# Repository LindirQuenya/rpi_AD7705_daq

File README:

Test / demo program for the AD7705 connected to the raspberry PI!
=================================================================

The AD7705 is a two channel sigma delta converter which has
differential inputs, a PGA and programmable data rates. It's
perfect for slowly changing inputs such as pressure, temperature,
heart rate etc.

The program is interrupt driven and can thus run in a thread
which is woken up by the interrupt. The clock for the ADC is
generated by directly manipulating the registers of the BCM
chip.

This program switches on the clock from the RPI, 
triggers a calibration of the AD, 
reads data from channel 1 and 
prints it on the screen.

This program uses DRDY connected to Port 22 and
waits for a falling edge on this port to read
the data. This is done via interrupts / poll
so that this process sleeps until new data becomes
available.

The design files are in the subdirectory "pcb".

To build:

    make

Run it with the command:

    sudo ./ad7705_test

Associated website:
http://web.eng.gla.ac.uk/rpi/

Bernd Porr
mail@berndporr.me.uk
www.berndporr.me.uk

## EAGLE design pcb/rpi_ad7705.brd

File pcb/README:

This work is licensed under a Creative Commons Attribution-NonCommercial 3.0 Unported License.
(C) 2013-2020 BERND PORR, www.berndporr.me.uk

This is an extension board which adds two analogue inputs to the Raspberry PI.
Three GPIO pins are also forwarded to another pin header with additional
input protection.

The AD7705 is a high preceision sigma delta converter with differential
inputs, buffers and a PGA. It's especially designed to measure small voltages,
for example from a pressure gauge or a thermocpuple.

The maximum sampling rate is 500Hz.

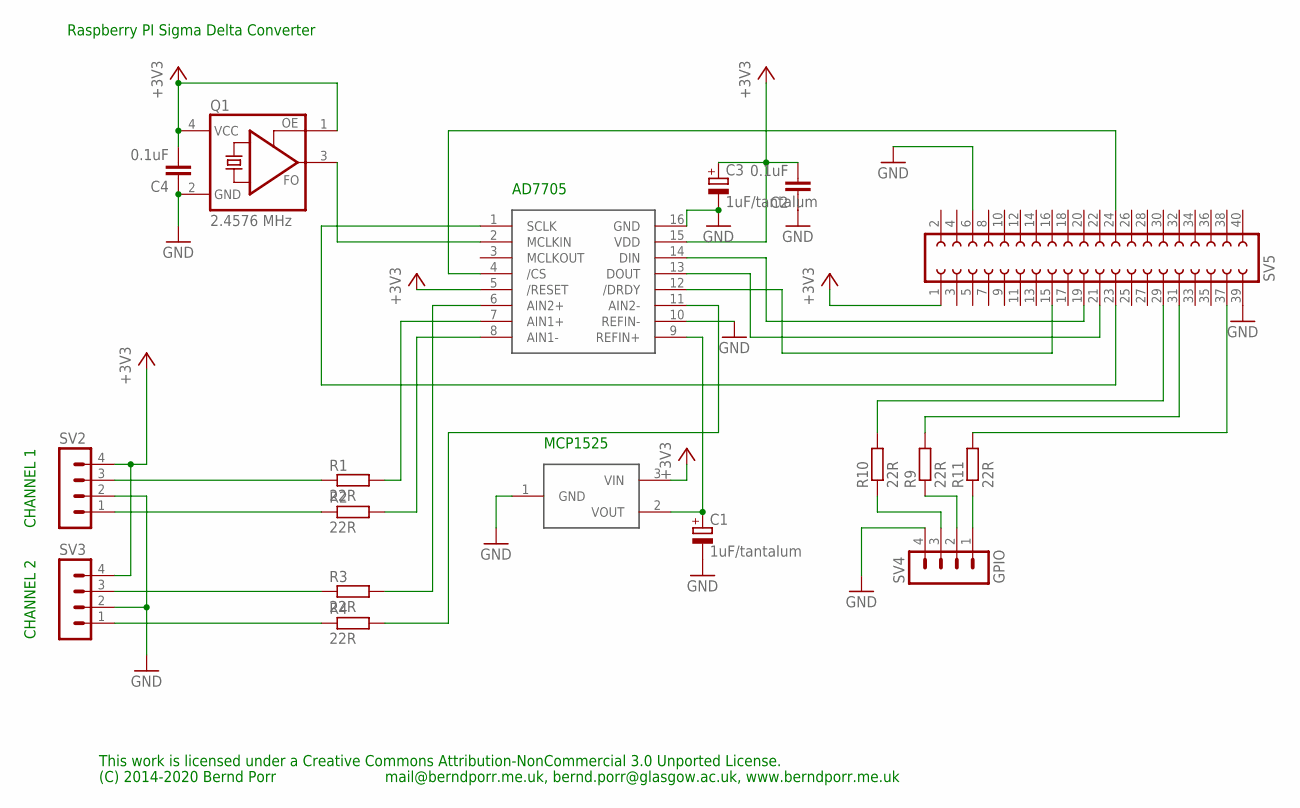
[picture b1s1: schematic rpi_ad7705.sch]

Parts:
C1, C3: 1uF/tantalum; TT2D7
C2, C4: 0.1uF; C5B2.5
Q1: 2.4576 MHz; ASF
R1, R2, R3, R4, R9, R10, R11: 22R; 0207/10
SV2, SV3: MA04-1
SV4: GPIO; MA04-1
SV5: FE20-2
U$1: AD7705; DIP16
U$2: MCP1525; TO92

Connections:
+3V3: C2.2, C3.+, C4.2, Q1.1 (OE), Q1.4 (VCC), SV2.4, SV3.4, SV5.1, U$1.5 (/RESET), U$1.15 (VDD), U$2.3 (VIN)
GND: C1.-, C2.1, C3.-, C4.1, Q1.2 (GND), SV2.2, SV3.2, SV4.4, SV5.6, SV5.39, U$1.10 (REFIN-), U$1.16 (GND), U$2.1 (GND)
unnamed: SV5.19, U$1.14 (DIN)
unnamed: SV5.23, U$1.1 (SCLK)
unnamed: Q1.3 (FO), U$1.2 (MCLKIN)
unnamed: SV5.24, U$1.4 (/CS)
unnamed: R11.2, SV5.37
unnamed: SV5.21, U$1.13 (DOUT)
unnamed: R2.2, U$1.8 (AIN1-)
unnamed: R1.2, U$1.7 (AIN1+)
unnamed: R3.2, U$1.6 (AIN2+)
unnamed: R4.2, U$1.11 (AIN2-)
unnamed: R1.1, SV2.3
unnamed: R2.1, SV2.1
unnamed: R3.1, SV3.3
unnamed: R4.1, SV3.1
unnamed: R10.1, SV4.3
unnamed: R9.2, SV5.31
unnamed: R10.2, SV5.29
unnamed: R11.1, SV4.1
unnamed: R9.1, SV4.2
unnamed: SV5.15, U$1.12 (/DRDY)
unnamed: C1.+, U$1.9 (REFIN+), U$2.2 (VOUT)

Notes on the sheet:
This work is licensed under a Creative Commons Attribution-NonCommercial 3.0 Unported License.
(C) 2014-2020 Bernd Porr
mail@berndporr.me.uk, bernd.porr@glasgow.ac.uk, www.berndporr.me.uk
AD7705
MCP1525
CHANNEL 1
CHANNEL 2
Raspberry PI Sigma Delta Converter

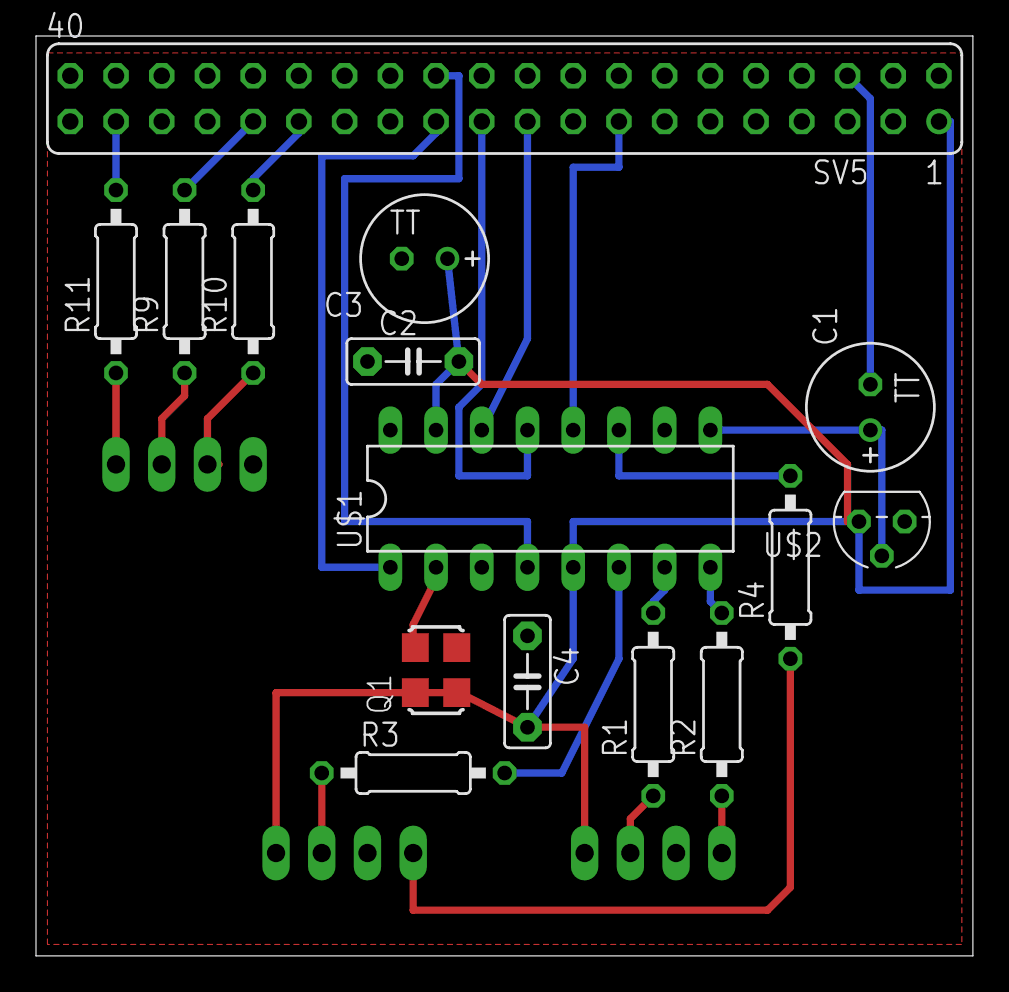
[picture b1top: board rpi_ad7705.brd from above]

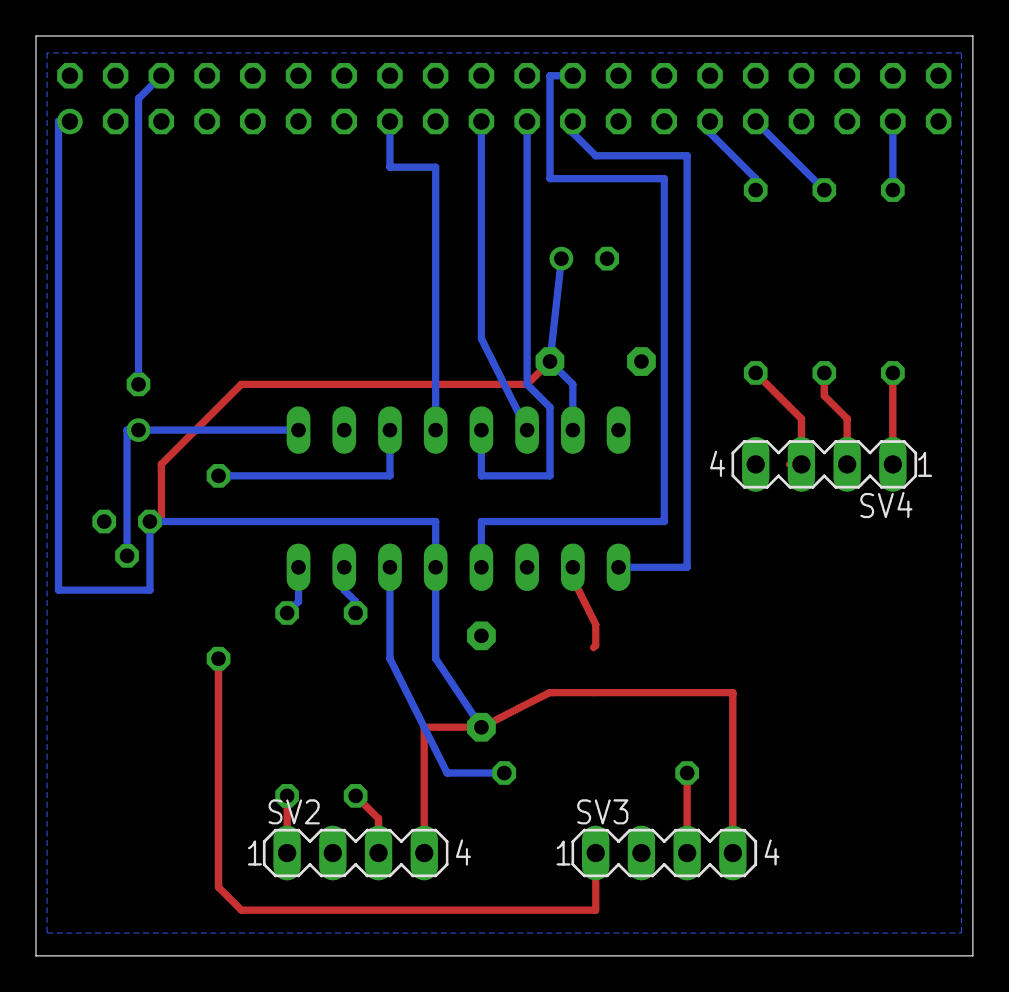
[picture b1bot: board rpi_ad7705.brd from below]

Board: 2 copper layers, 52.0 x 51.1 mm, 18 parts (3 on the bottom side), 23 nets.

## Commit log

2014-02-14 Polling is now done via the GPIO pin 22 which connects to the DRDY pin of the AD converter. This should speed up reading from the AD drastically.
2014-02-22 Now using interrupts and the gpio handling is done in the files gpio-sysfs.*
2016-02-05 This program no longer worked with Jessie because the kernel does now stricter checks on the SPI commands. In particular the struct spi_ioc_transfer needs to be set to zero via memset in all location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
2016-02-05 Updated the README
2018-01-30 Fixed SPI comms which requires now to specify speed and delay for every tranfer.
2018-01-30 Tidied up things. It looked terrible before.
2018-01-30 Updated the copyright
2018-02-02 Added the PCB design files
2018-02-02 Changed to markup
2018-02-02 changed title
2020-01-29 Made a start to make it proper object oriented
2020-01-29 Now properly with callbacks and the whole ADC routine in a class and thread.
2020-01-30 Forgotten cmake
2020-01-30 Added info about sampling rate.
2020-01-30 Updated tab stops etc
2020-01-30 Added sampling rate setting
2020-01-30 Changed to pointers in the demo program
2020-01-30 Callback hander just as an instance
2020-01-30 Updated circuit with an oscillator and new pin header.
2020-01-30 Switched the molex to the other side
2020-01-30 The bcm library is no longer needed
2020-02-04 Clock source is now from external oscillator and no longer from the RPI so that it can run as a normal user
2020-02-04 removed the evil bcm library
2020-03-17 Added UDP transfer
2020-03-18 Updated README and added a signal handler for HUP
2020-03-19 Now with dygraph
2020-03-19 Fixed date format
2020-03-19 Timestamping is now down to a ms.
2020-03-19 Added the new files for dygraphs
2020-03-19 Also updating the text at the top.
2020-03-20 Displays cached data in case UDP fails and is not crashing.
2020-03-21 Added info about the websites.
2020-03-21 Added info about PHP.
2020-03-28 Made the design responsive.
2020-03-29 Added screenshot
2020-03-29 Added the screenshot
2020-03-29 Made clear that we have JSON and file management.
2020-04-06 Removed a spurious "sudo".
2021-03-20 Added fastcgi code to it
2021-03-20 FastCGI works
2021-03-21 Updated it for FastCGI
2021-03-21 Added character encoding and removed the local IP address
2021-03-21 Beautified the code a bit
2021-03-21 Put the fastCGI stuff in a class with a callback handler and showed how to transmit data between different handlers.
2021-03-21 Got rid of an akward string construct
2021-03-21 Got rid of the old UDP
2021-03-21 Moved the fastCGI functionality to a header file
2021-03-21 Tidied things up
2021-03-21 Updated with dygraph
2021-03-21 Fixed link to the text-only page
2021-03-21 Integers have no decimal points...
2021-03-21 Default format is now json
2021-03-21 Added some more comments to the code.
2021-03-22 Added check for GET.
2021-03-22 Now also with POST so that a button can send stuff over.
2021-03-22 No longer needed
2021-03-22 Updated the website stuff here on git
2021-03-23 Moved the JSON decoding also into a function.
2021-03-23 New naming
2021-03-23 Changed the order
2021-03-23 Prevent crash if req length not set
2021-03-23 Made the textonly file more readable.
2021-03-25 Updated header here
2021-03-25 Keep header in sync
2021-03-25 Got rid of the json_fastcgi_web_api.h here and rather check it out from the other repo.
2021-03-25 Tidied up README and added submodule
2021-03-25 Updated it to the newest json_fastcgi library now with CURL!
2021-03-25 Keeping track
2021-03-25 Reference to the data dir
2021-03-25 It's /data.
2021-03-25 Updated so that it tracks the current submodule
2021-03-25 Updated to newest json_fastcgi_web_api.
2021-03-25 Updated to newest json_fastcgi_web_api
2021-03-31 Made is more readable
2021-03-31 Move the script to the header.
2022-02-12 Added missing package info
2022-02-14 Also implemented the new class
2022-02-15 Changed sampling rate to an enum
2022-02-15 Added docs
2022-02-15 Added pointer to the online docs
2022-02-15 Added parameters
2022-02-15 Updated online docs
2022-02-16 Added more options to configure it
2022-02-16 Updated api so that real values are used
2022-02-16 Added the pga gain
2022-02-16 Updated the docs
2022-02-18 Created subdir for the demo
2022-02-18 Upd readme
2022-02-18 Removed old folder
2022-02-18 Fixed formatting
2022-02-19 UDP leftover
2022-02-20 Name change
2022-02-22 Absorbed the sysfs into the main class
2022-02-22 Got rid of warnings
2022-02-22 Added more debug msg
2022-02-22 fixed doc
2022-02-22 Documentation was missing
2022-02-22 Fixed comment.
2022-02-22 Regenerated docs
2022-03-02 More in line with the handout
2023-03-02 Got rid of the static function for the thread
2023-06-05 Don't discard settings in constructor.
